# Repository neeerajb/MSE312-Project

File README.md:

# MSE312-Project
This project is the design for my MSE 312 course held in Simon Fraser University.

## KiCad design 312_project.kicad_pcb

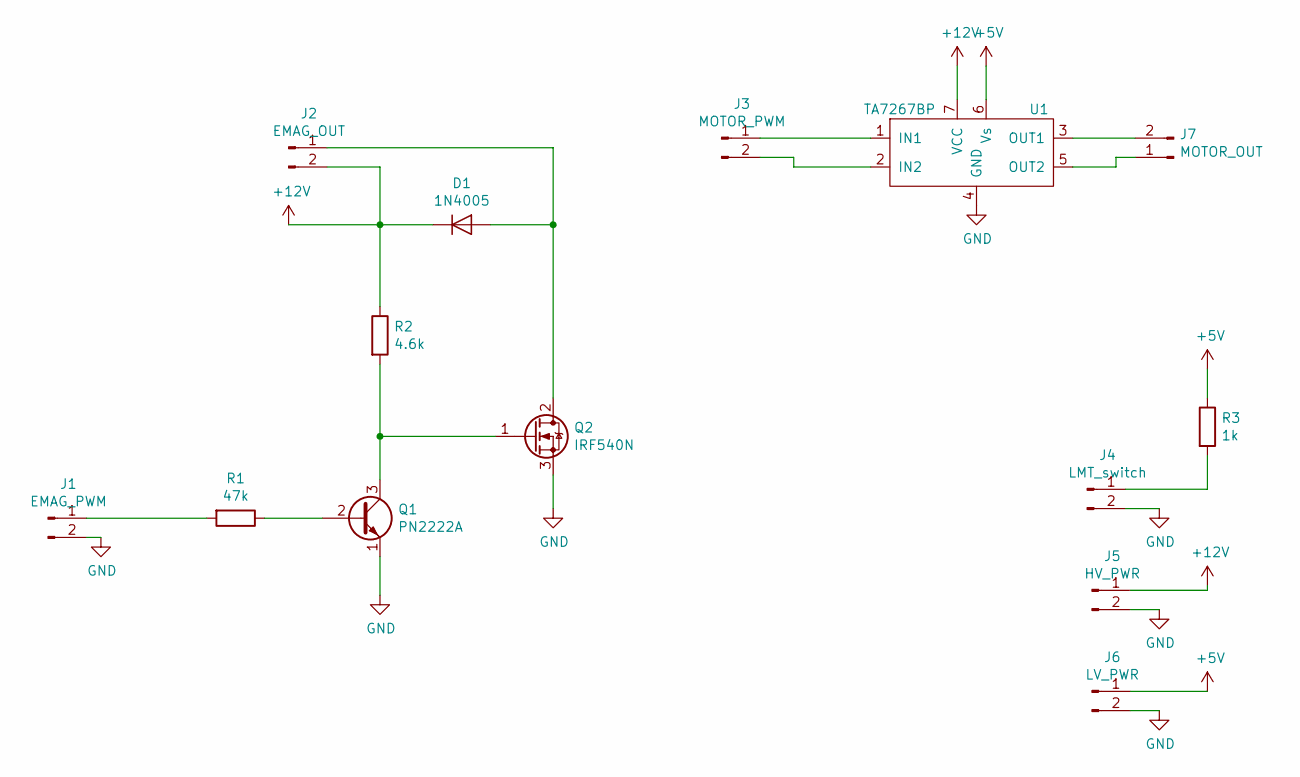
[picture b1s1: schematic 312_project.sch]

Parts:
D1: 1N4005; D_DO-41_SOD81_P10.16mm_Horizontal
J1: EMAG_PWM; Pin_Header_Straight_1x02_Pitch2.00mm
J2: EMAG_OUT; Pin_Header_Straight_1x02_Pitch2.00mm
J3: MOTOR_PWM; Pin_Header_Straight_1x02_Pitch2.00mm
J4: LMT_switch; Pin_Header_Straight_1x02_Pitch2.00mm
J5: HV_PWR; Pin_Header_Straight_1x02_Pitch2.00mm
J6: LV_PWR; Pin_Header_Straight_1x02_Pitch2.00mm
J7: MOTOR_OUT; Pin_Header_Straight_1x02_Pitch2.00mm
Q1: PN2222A; TO-92_Horizontal2_Inline_Narrow_Oval
Q2: IRF540N; TO-92_Horizontal2_Inline_Narrow_Oval
R1: 47k; R_Axial_DIN0309_L9.0mm_D3.2mm_P15.24mm_Horizontal
R2: 4.6k; R_Axial_DIN0309_L9.0mm_D3.2mm_P15.24mm_Horizontal
R3: 1k; R_Axial_DIN0309_L9.0mm_D3.2mm_P15.24mm_Horizontal
U1: TA7267BP; R_Array_SIP7

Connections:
+5V: J6.1, R3.1, U1.6 (Vs)
+12V: D1.1 (K), J2.2, J5.1, R2.1, U1.7 (VCC)
GND: J1.2, J4.2, J5.2, J6.2, Q1.1 (E), Q2.3 (S), U1.4 (GND)
unnamed: D1.2 (A), J2.1, Q2.2 (D)
unnamed: J1.1, R1.2
unnamed: J3.1, U1.1 (IN1)
unnamed: J3.2, U1.2 (IN2)
unnamed: J4.1, R3.2
unnamed: J7.1, U1.5 (OUT2)
unnamed: J7.2, U1.3 (OUT1)
unnamed: Q1.2 (B), R1.1
unnamed: Q1.3 (C), Q2.1 (G), R2.2

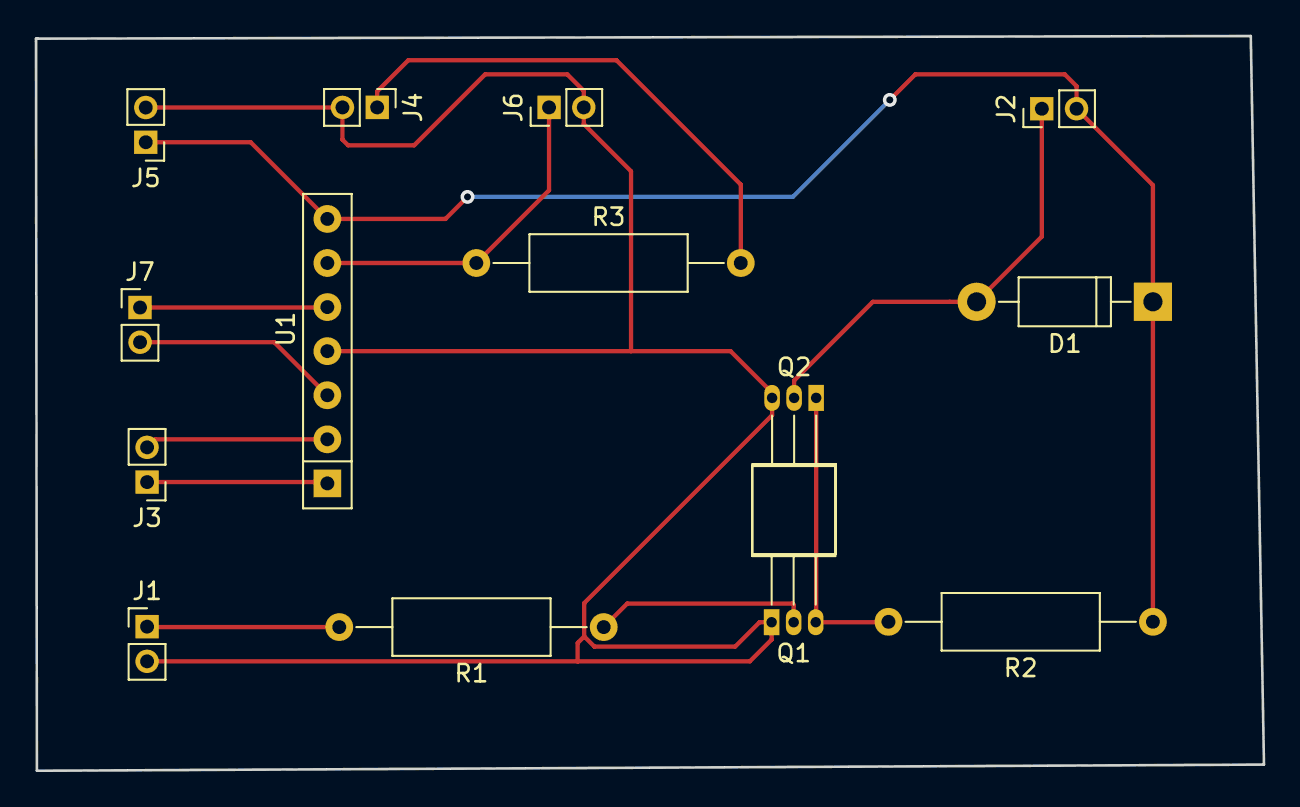
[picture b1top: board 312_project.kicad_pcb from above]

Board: 2 copper layers, 70.8 x 42.3 mm, 14 parts (0 on the bottom side), 12 nets.

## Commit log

2019-06-27 uploading files
2019-07-04 added power protection circuit
